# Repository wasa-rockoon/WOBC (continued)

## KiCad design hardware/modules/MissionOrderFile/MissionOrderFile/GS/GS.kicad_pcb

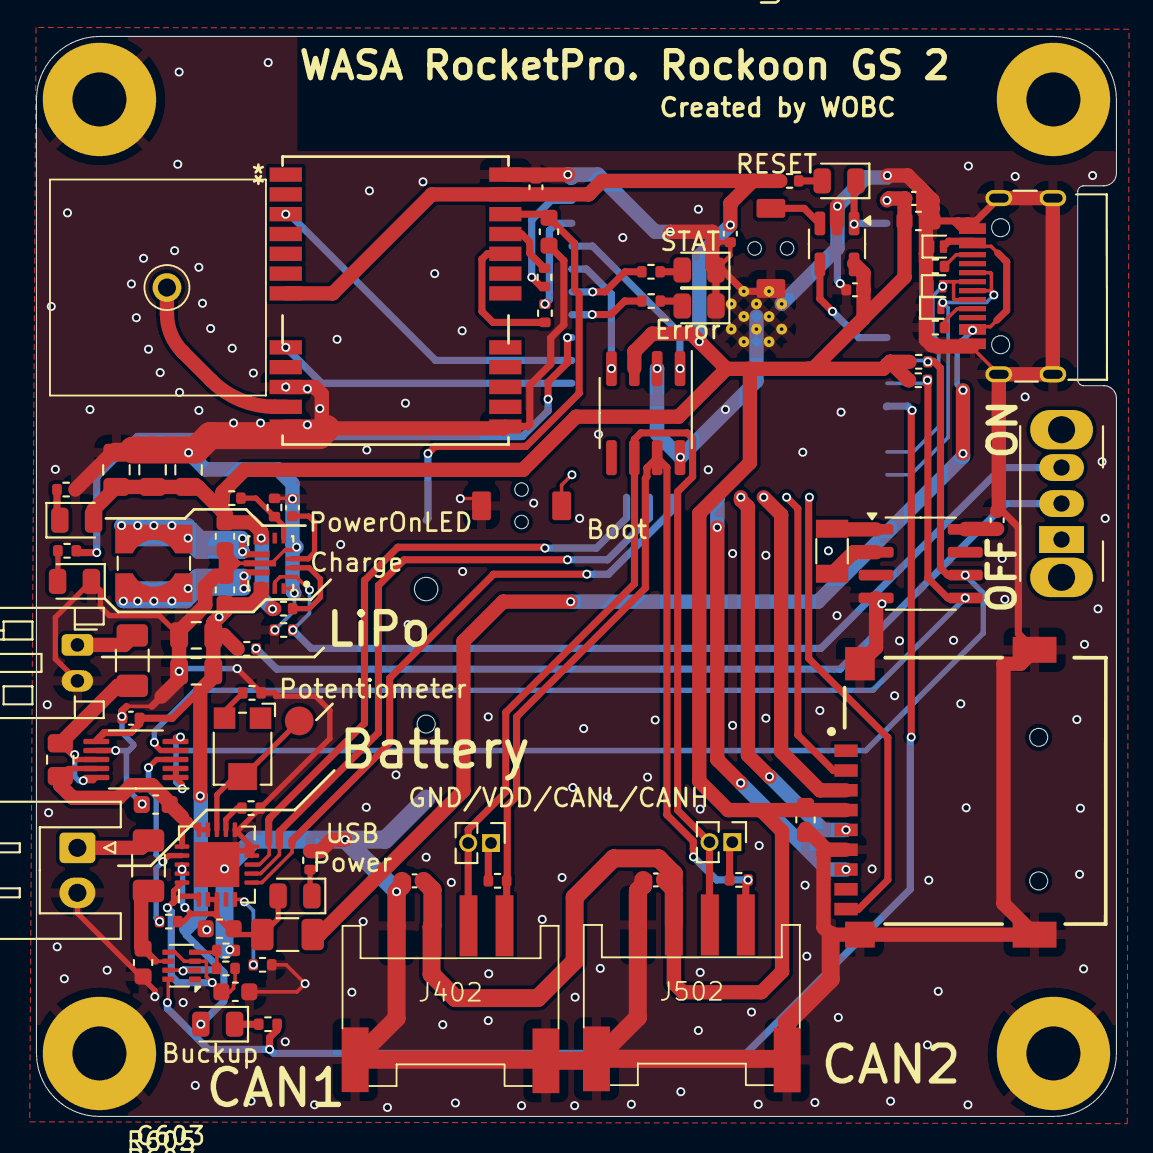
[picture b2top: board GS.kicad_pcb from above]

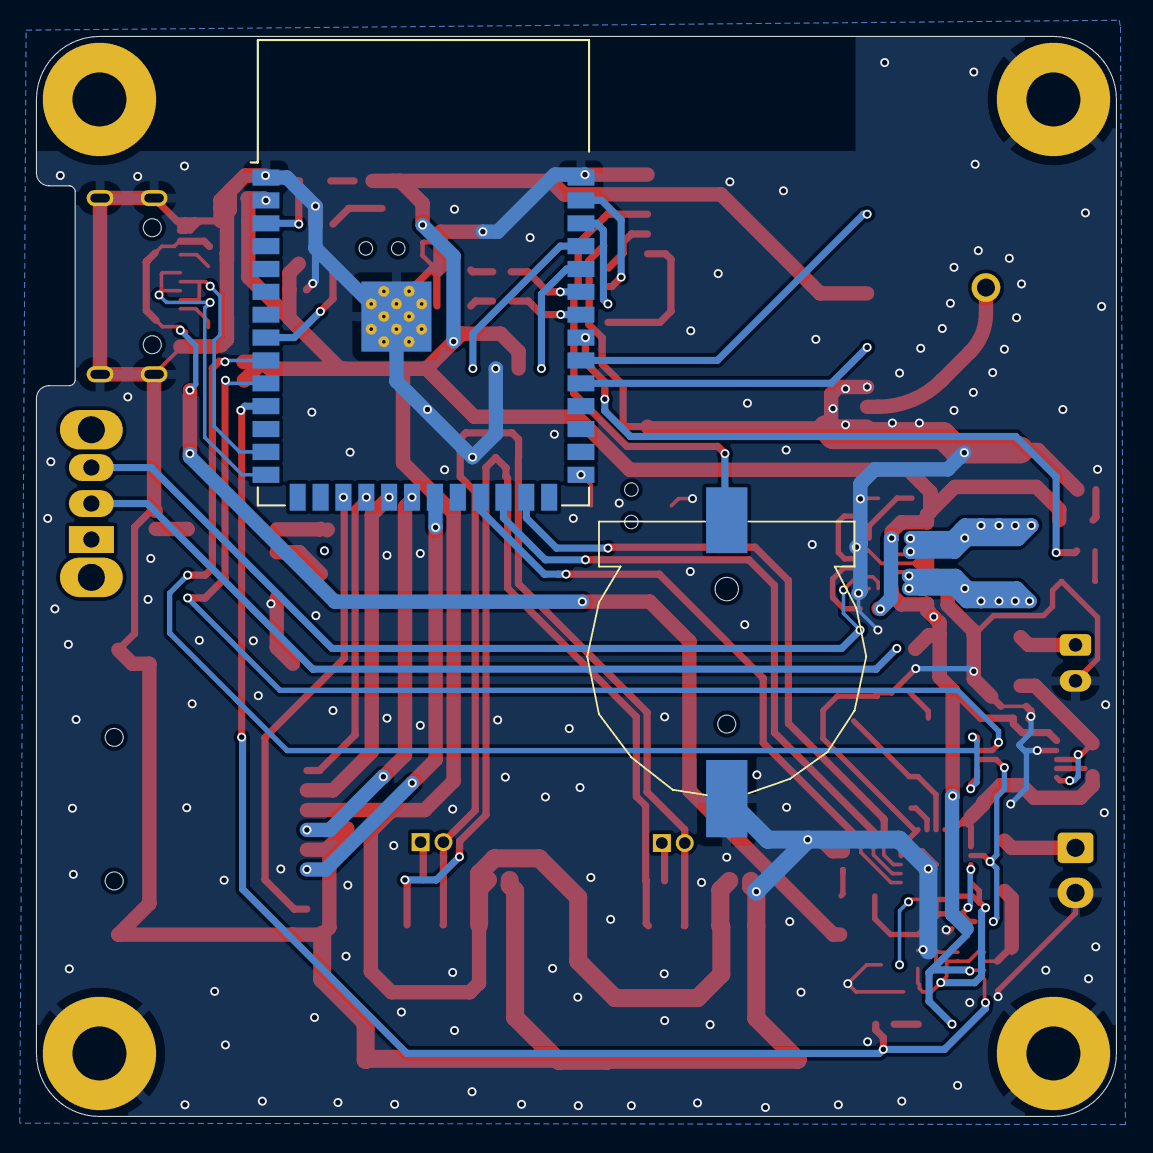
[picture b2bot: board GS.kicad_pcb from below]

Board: 2 copper layers, 60.0 x 60.0 mm, 88 parts (2 on the bottom side), 70 nets.

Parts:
AE301: Antenna; GNSS_Antenna_1212
BT101: Battery; cr1220
C101, C203, C601, C602, C603, C606, C607, C610, C701: 10uF; C_0603_1608Metric
C201, C202, C204, C301, C401, C501, C608, C609, C702: 100nF; C_0402_1005Metric
C604, C605, C611, C612, C613: 10uF; C_0805_2012Metric
D201, D202, D203: 5V; D_SOD-882
D204: RESET; LED_0805_2012Metric
D205: ERROR; LED_0805_2012Metric
D206: STAT; LED_0805_2012Metric
F601, F602, F603: Polyfuse; Fuse_1206_3216Metric
J401, J501: Jumper; PinHeader_1x02_P1.27mm_Vertical
J402, J502: Conn_01x04_MountingPin; Grove_4P_L_SMD
J601: Battery; JST_XH_S2B-XH-A_1x02_P2.50mm_Horizontal
J602: LiPo; JST_PH_S2B-PH-K_1x02_P2.00mm_Horizontal
L601: L; L_Wuerth_WE-TPC-3816
LED601: USB Power; LED_0805_2012Metric
LED602: Backup; LED_0805_2012Metric
LED603: CHARGE; LED_0805_2012Metric
LED604: VDD; LED_0805_2012Metric
MICRO_SD701: TF-01A
R201, R202: 5.1k; R_0402_1005Metric
R203, R204, R206: 470; R_0402_1005Metric
R205, R207, R604, R609: 10k; R_0402_1005Metric
R301, R302: 33; R_0402_1005Metric
R401, R501: 120; R_0402_1005Metric
R601, R602, R608, R610, R616: 1k; R_0402_1005Metric
R603, R606, R607, R611, R613: 100k; R_0402_1005Metric
R605, R615: 47k; R_0402_1005Metric
R612: 50mΩ; R_0805_2012Metric
R614: 15k; R_0402_1005Metric
RV601: 10k; Potentiometer_Bourns_TC33X_Vertical
SW201, SW202: RESET_sw; TVAF06-A020B-R
SW601: Power Switch; SW_Slide_SPDT_Angled_CK_OS102011MA1Q
U201: TPS3820; SOT-23-5
U202: SN65HVD230; SOIC-8_3.9x4.9mm_P1.27mm
U203: ESP32-S3-WROOM-1
U301: NEO-M9N-00B; ATGM332D-5N31
U601: MCP73871-1CC; QFN-20-1EP_4x4mm_P0.5mm_EP2.5x2.5mm
U602: TPS2116DRL; SOT-583-8
U603: TPS63070RNMR; VREG_TPS63070RNMR
U604: INA226; VSSOP-10_3x3mm_P0.5mm
U701: PCF8563T; SOIC-8_3.9x4.9mm_P1.27mm
USB201: USB_C_Receptacle_USB2.0; USB_C_TYPEC-301S-ACP16X7
Y701: Crystal; Crystal_SMD_3215-2Pin_3.2x1.5mm

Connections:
+BATT: C702.2, U701.8 (VDD)
/CLK: MICRO_SD701.5 (CLK), U203.20 (GPIO12/TOUCH12/ADC2_CH1/FSPICLK/FSPIIO6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)
/DET: MICRO_SD701.CD1 (CD), U203.17 (GPIO9/TOUCH9/ADC1_CH8/FSPIHD/SUBSPIHD)
/ESP32/CANH: J402.1, J502.1, R401.2, R501.2, U202.7 (CANH)
/ESP32/CANL: J401.2, J402.2, J501.2, J502.2, U202.6 (CANL)
/ESP32/CAN_RX: U202.4 (R), U203.36 (U0RXD/GPIO44/CLK_OUT2)
/ESP32/CAN_TX: U202.1 (D), U203.37 (U0TXD/GPIO43/CLK_OUT1)
/ESP32/GPIO1/ADC1_CH0: R301.1, U203.39 (GPIO1/TOUCH1/ADC1_CH0)
/ESP32/GPIO2/ADC1_CH1: R302.1, U203.38 (GPIO2/TOUCH2/ADC1_CH1)
/ESP32/GPIO18: R608.2, U203.11 (GPIO18/U1RXD/ADC2_CH7/CLK_OUT3), U602.8 (ST)
/ESP32/GPIO38: U203.31 (GPIO38/FSPIWP/SUBSPIWP), U301.8 (RESET_N)
/ESP32/GPIO39: U203.32 (MTCK/GPIO39/CLK_OUT3/SUBSPICS1), U301.3 (TIMEPULSE)
/ESP32/GPIO40: R610.2, U203.33 (MTDO/GPIO40/CLK_OUT2)
/ESP32/USB_D+: D202.2 (A2), U203.14 (GPIO20/U1CTS/ADC2_CH9/CLK_OUT1/USB_D+), USB201.A6 (D+), USB201.B6 (D+)
/ESP32/USB_D-: D203.2 (A2), U203.13 (GPIO19/U1RTS/ADC2_CH8/CLK_OUT2/USB_D-), USB201.A7 (D-), USB201.B7 (D-)
/ESP32/VUSB: D201.2 (A2), F601.1, USB201.A4 (VBUS), USB201.A9 (VBUS), USB201.B4 (VBUS), USB201.B9 (VBUS)
/ESP32/WDI: U201.4 (WDI), U203.8 (GPIO15/U0RTS/ADC2_CH4/XTAL_32K_P)
/GPS/+BATT: BT101.1 (+), C101.2, U301.22 (V_BCKP)
/MISO: MICRO_SD701.7 (DAT0), U203.21 (GPIO13/TOUCH13/ADC2_CH2/FSPIQ/FSPIIO7/S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)
/MOSI: MICRO_SD701.3 (CMD), U203.19 (GPIO11/TOUCH11/ADC2_CH0/FSPID/FSPIIO5/S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)
/PG: U203.23 (GPIO21), U601.6 (~PG)
/SCL: R205.2, U203.9 (GPIO16/U0CTS/ADC2_CH5/XTAL_32K_N), U604.1 (A1), U604.2 (A0), U604.5 (SCL), U701.6 (SCL)
/SDA: R207.2, U203.10 (GPIO17/U1TXD/ADC2_CH6), U604.4 (SDA), U701.5 (SDA)
/SS: MICRO_SD701.2 (CD/DAT3), U203.18 (GPIO10/TOUCH10/ADC1_CH9/FSPICS0/FSPIIO4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)
/STAT1: U203.25 (GPIO48/SPICLK_N/SUBSPICLK_N_DIFF), U601.8 (STAT1/~LBO)
/STAT2: U203.24 (GPIO47/SPICLK_P/SUBSPICLK_P_DIFF), U601.7 (STAT2)
GND: BT101.2 (-), C101.1, C201.1, C202.1, C203.1, C204.2, C301.1, C401.1, C501.1, C601.2, C602.2, C603.2, C604.2, C605.2, C606.2, C607.2, C608.2, C609.2, C610.2, C611.2, C612.2, C613.2, C701.2, C702.1, D201.1 (A1), D202.1 (A1), D203.1 (A1), D205.1 (K), D206.1 (K), J402.4, J402.MP (MountPin), J502.4, J502.MP (MountPin), J601.2, J602.2, LED603.1 (K), MICRO_SD701.6 (VSS), MICRO_SD701.MP1 (SHIELD), MICRO_SD701.MP2 (SHIELD), MICRO_SD701.MP3 (SHIELD), MICRO_SD701.MP4 (SHIELD), R201.2, R202.2, R601.2, R602.2, R603.2, R604.1, R605.1, R611.2, R614.1, R616.2, SW201.2, SW202.2, U201.2 (GND), U202.2 (GND), U202.8 (Rs), U203.1 (GND), U203.40 (GND), U203.41 (GND), U301.10 (GND), U301.12 (GND), U301.13 (GND), U301.24 (GND), U601.9 (~TE), U601.10 (V_{SS}), U601.11 (V_{SS}), U601.21 (V_{SS}), U602.1 (GND), U603.4 (GND), U603.10 (PGND), U603.15 (VSEL), U604.7 (GND), U701.4 (VSS), USB201.A1 (GND), USB201.A12 (GND), USB201.B1 (GND), USB201.B12 (GND), USB201.S1 (SHIELD)
GPSANT1: AE301.1 (A), U301.11 (RF_IN)
unnamed: D204.2 (A), R203.2
unnamed: D205.2 (A), R204.2
unnamed: D206.2 (A), R206.2
unnamed: J401.1, R401.1
unnamed: J501.1, R501.1
unnamed: F602.1, J601.1
unnamed: F603.2, J602.1
unnamed: C601.1, F601.2, LED601.2 (A), R606.1, U601.2 (VPCC), U601.3 (SEL), U601.18 (IN), U601.19 (IN)
unnamed: LED601.1 (K), R601.1
unnamed: C604.1, C605.1, C607.1, C608.1, LED602.2 (A), R609.1, U602.2 (VOUT), U602.7 (VOUT), U603.12_13 (VIN), U604.6 (VS)
unnamed: LED602.1 (K), R608.1
unnamed: LED603.2 (A), R610.1
unnamed: LED604.1 (K), R616.1
unnamed: R602.1, RV601.3
unnamed: R609.2, SW601.2 (B)
unnamed: R611.1, SW601.3 (C), U603.1 (PS/SYNC), U603.14 (EN)
unnamed: SW201.1, U201.3 (MR)
unnamed: SW202.1, U203.27 (GPIO0/BOOT)
unnamed: R204.1, U203.34 (MTDI/GPIO41/CLK_OUT1)
unnamed: R206.1, U203.35 (MTMS/GPIO42)
unnamed: R301.2, U301.21 (RXD_/_SPI_MOSI)
unnamed: R302.2, U301.20 (TXD_/_SPI_MISO)
unnamed: R606.2, U601.17 (CE), U604.3 (~Alert)
unnamed: RV601.2, U601.13 (PROG1)
unnamed: R603.1, U601.12 (PROG3)
unnamed: R604.2, U601.5 (THERM)
unnamed: C606.1, R612.1, U601.14 (V_{BAT}), U601.15 (V_{BAT}), U601.16 (V_{BAT_SENSE}), U604.9 (Vin-)
unnamed: C603.1, R607.1, U601.1 (OUT), U601.20 (OUT), U602.3 (VIN1), U602.5 (MODE)
unnamed: R605.2, R607.2, U602.4 (PR1)
unnamed: C602.1, F602.2, U602.6 (VIN2)
unnamed: R614.2, R615.1, U603.5 (FB)
unnamed: L601.1, U603.11 (L1)
unnamed: L601.2, U603.9 (L2)
unnamed: R613.2, U603.2 (PG)
unnamed: C609.1, U603.3 (VAUX)
unnamed: F603.1, R612.2, U604.8 (Vbus), U604.10 (Vin+)
unnamed: U701.1 (OSCI), Y701.1
unnamed: U701.2 (OSCO), Y701.2
unnamed: R201.1, USB201.A5 (CC1)
unnamed: R202.1, USB201.B5 (CC2)
RESET: D204.1 (K), U201.1 (RESET), U203.3 (EN)
VDD: C201.2, C202.2, C203.2, C204.1, C301.2, C401.2, C501.2, C610.1, C611.1, C612.1, C613.1, C701.1, J402.3, J502.3, LED604.2 (A), MICRO_SD701.4 (VDD), R203.1, R205.1, R207.1, R613.1, R615.2, U201.5 (VDD), U202.3 (VCC), U203.2 (3V3), U301.7 (V_USB), U301.23 (VCC), U603.7_8 (VOUT)

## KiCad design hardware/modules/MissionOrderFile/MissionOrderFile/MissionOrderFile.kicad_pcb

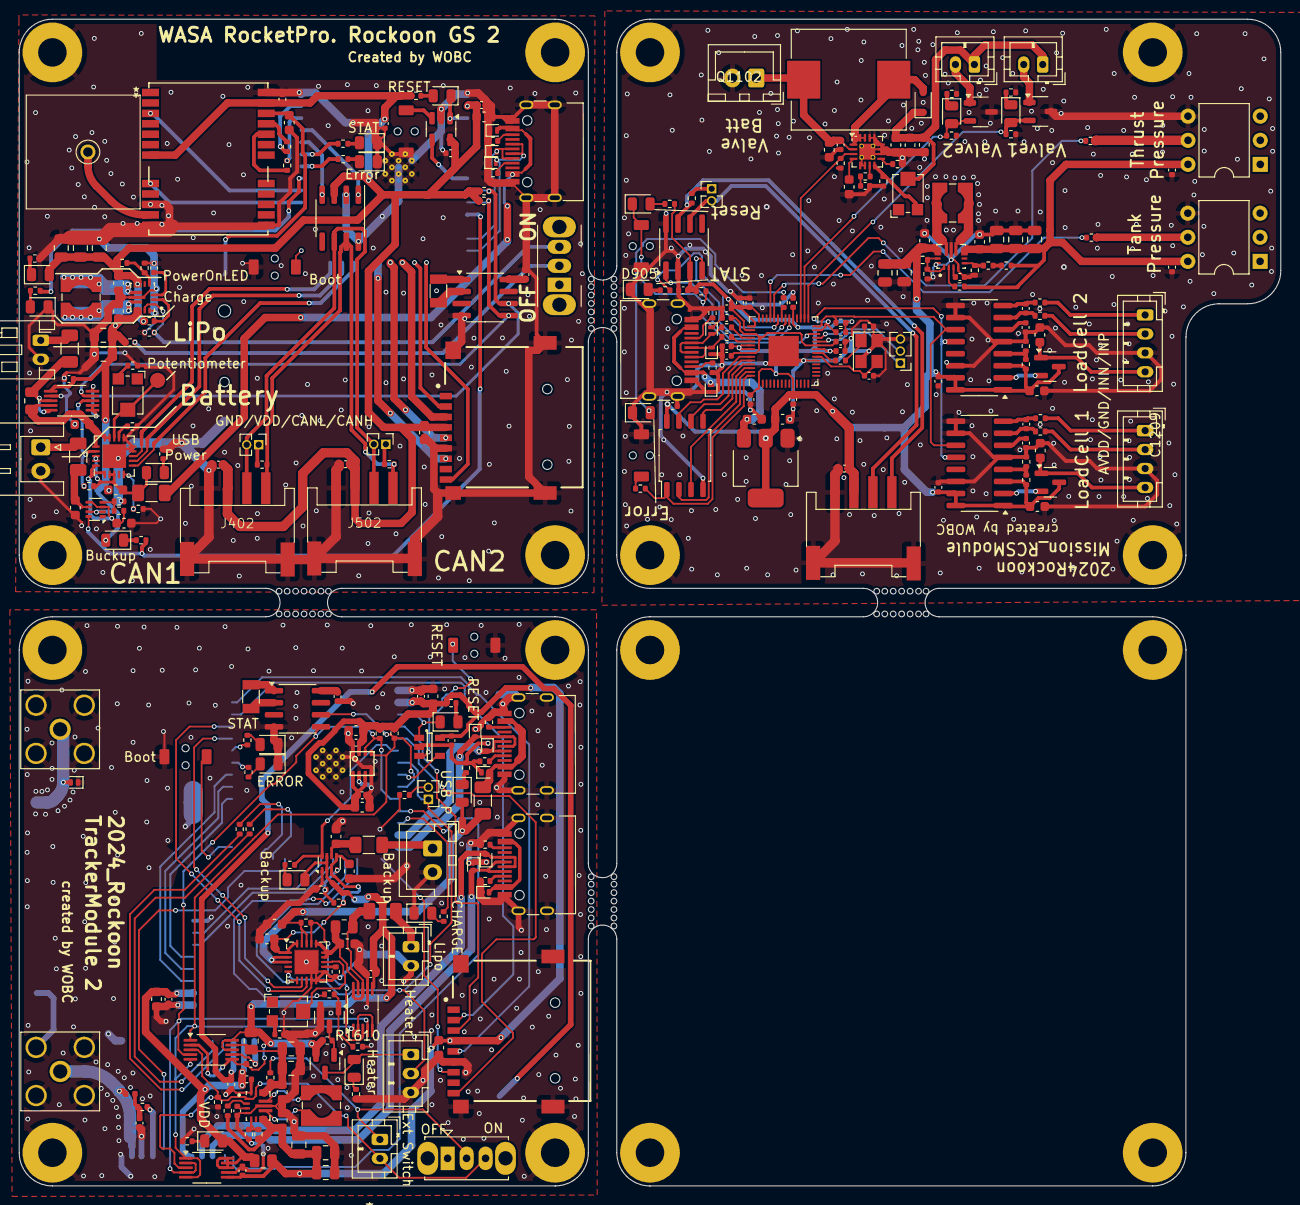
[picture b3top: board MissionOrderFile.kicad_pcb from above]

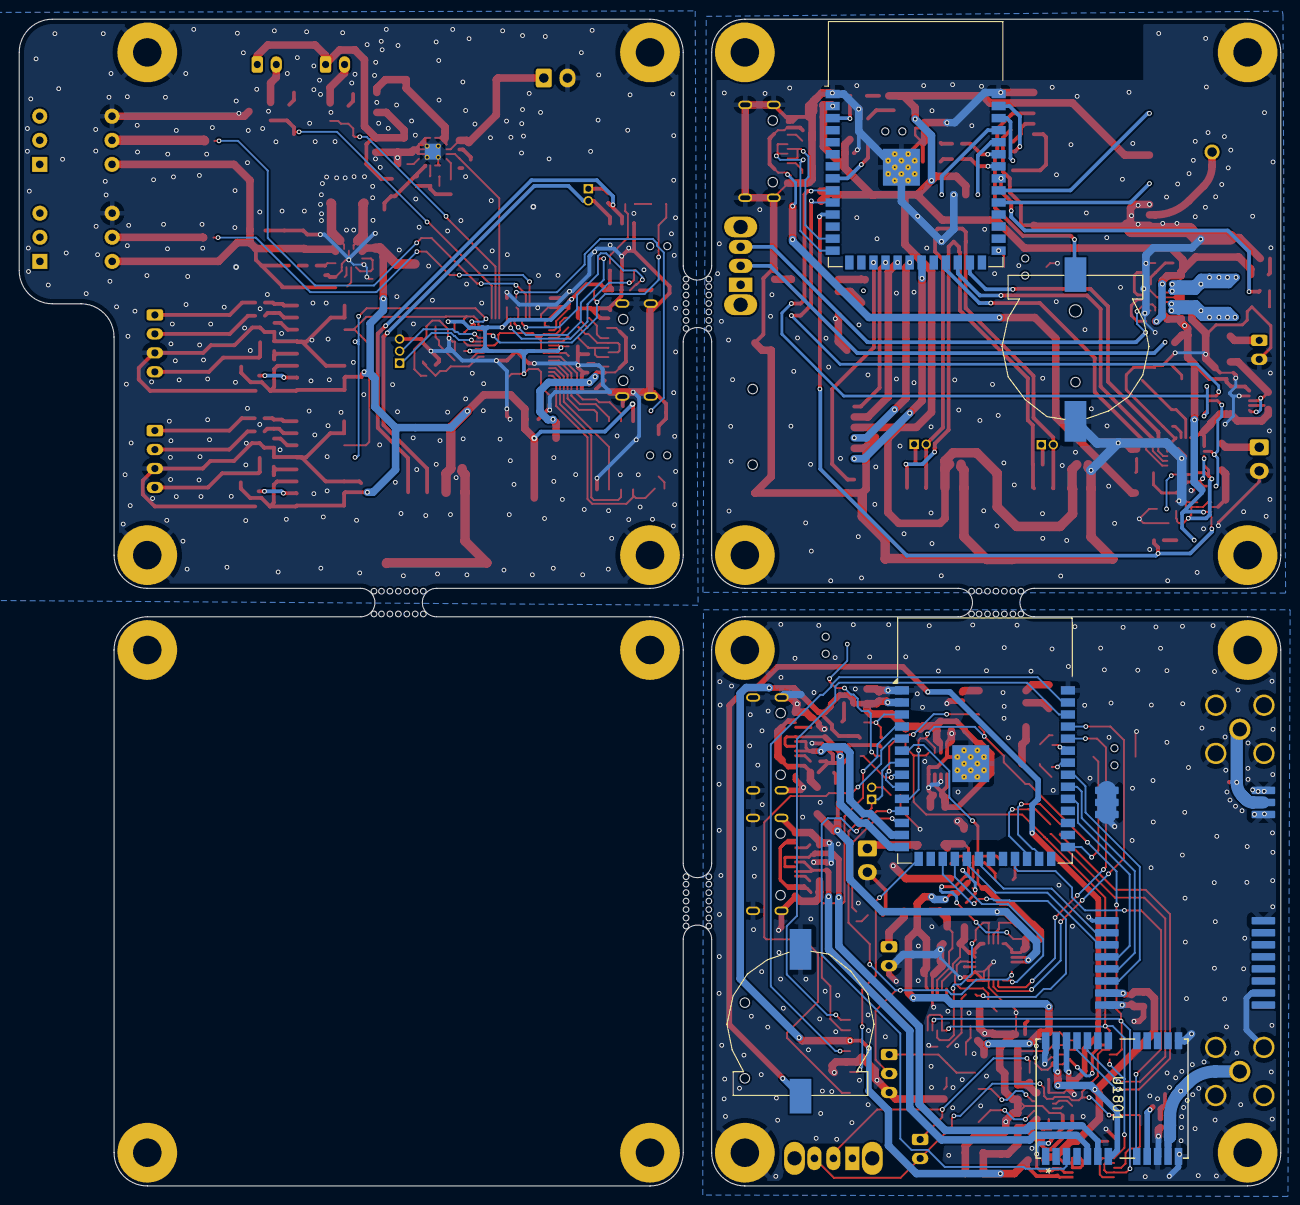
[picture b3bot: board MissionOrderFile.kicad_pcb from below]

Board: 2 copper layers, 133.0 x 123.0 mm, 322 parts (6 on the bottom side), 224 nets.

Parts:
AE301: Antenna; GNSS_Antenna_1212
BT101: Battery; cr1220
BT1501: Battery_Cell; cr1220
C101, C203, C601, C602, C603, C606, C607, C610, C701, C1102, C1203, C1205, C1301, C1304, C1401, C1404, C1601, C1602, C1603, C1605, C1606, C1610, C1612, C1901, C2102: 10uF; C_0603_1608Metric
C201, C202, C204, C301, C401, C501, C608, C609, C702, C901, C902, C905, C906, C908, C910, C911, C912, C913, C914, C915, C1001, C1204, C1209, C1210, C1604, C1609, C1611, C1616, C1702, C1703, C1801, C1802, C1803, C1902, C2101, C2103: 100nF; C_0402_1005Metric
C604, C605, C611, C612, C613: 10uF; C_0805_2012Metric
C801, C802, C2001: 10u; C_0603_1608Metric
C903, C904: 27pF; C_0402_1005Metric
C907, C909: 1uF; C_0402_1005Metric
C1101: 47nF; C_0603_1608Metric
C1103, C1104, C1302, C1303, C1305, C1402, C1403, C1405: 0.1uF; C_0402_1005Metric
C1105, C1106, C1107: 4.7uF; C_0603_1608Metric
C1201, C1202, C1206, C1207, C1208, C1607, C1608, C1613, C1614, C1615: 22uF; C_0805_2012Metric
C1701, C1704: 10μF; C_0603_1608Metric
C2002: 100n; C_0402_1005Metric
D201, D202, D203, D902, D903, D904: 5V; D_SOD-882
D204, D901, D2104: RESET; LED_0805_2012Metric
D205, D906, D2105: ERROR; LED_0805_2012Metric
D206, D905, D2106: STAT; LED_0805_2012Metric
D1101: D; D_SOD-323
D1102, D1103: LED; D_0805_2012Metric
D1801, D1802, D1803, D2101, D2102, D2103: 5V; D_SOD-882D
D2001: ESD9B5.0ST5G; D_SOD-882D
F601, F602, F603, F1601, F1602, F1603: Polyfuse; Fuse_1206_3216Metric
J401, J501, J1001: Jumper; PinHeader_1x02_P1.27mm_Vertical
J402, J502, J1002: Conn_01x04_MountingPin; Grove_4P_L_SMD
J601: Battery; JST_XH_S2B-XH-A_1x02_P2.50mm_Horizontal
J602: LiPo; JST_PH_S2B-PH-K_1x02_P2.00mm_Horizontal
J801: Conn_01x02; JST_XH_B2B-XH-A_1x02_P2.50mm_Vertical
J901: DEBUG; PinHeader_1x03_P1.27mm_Vertical
J1101, J1102: Conn_01x02; JST_PH_B2B-PH-K_1x02_P2.00mm_Vertical
J1301, J1401: Conn_01x04; JST_PH_B4B-PH-K_1x04_P2.00mm_Vertical
J1601: Battery; JST_XH_B2B-XH-A_1x02_P2.50mm_Vertical
J1602: Temp&Heater; JST_PH_B3B-PH-K_1x03_P2.00mm_Vertical
J1603: Ext Switch; JST_PH_B2B-PH-K_1x02_P2.00mm_Vertical
J1604: HeaterPin; PinHeader_1x02_P1.27mm_Vertical
J1605: LiPo; JST_PH_B2B-PH-K_1x02_P2.00mm_Vertical
J1801, J2001: SMA; SMA_Amphenol_132203-12_Horizontal
L601, L1201, L1601: L; L_Wuerth_WE-TPC-3816
L1101: L; L_Chilisin_BMRF00101040
L1801: 27nH, 300mA; L_0402_1005Metric
LED601, LED1601: USB Power; LED_0805_2012Metric
LED602, LED1603: Backup; LED_0805_2012Metric
LED603, LED1602: CHARGE; LED_0805_2012Metric
LED604, LED1605: VDD; LED_0805_2012Metric
LED1604: Heater; LED_0805_2012Metric
MICRO_SD701, MICRO_SD1901: TF-01A
Q1101, Q1102: NMOS; SOT-23-3
Q1301, Q1401: PNP; SOT-23
Q1601: Q_NPN_BEC; SOT-23
Q1602: Q_PMOS_GSD; SOT-23
R201, R202, R903, R904, R1801, R1802, R2101, R2102: 5.1k; R_0402_1005Metric
R203, R204, R206, R2103, R2104, R2106: 470; R_0402_1005Metric
R205, R207, R604, R609, R901, R909, R911, R1201, R1204, R1304, R1404, R1608, R1611, R1614, R1615, R2105, R2107: 10k; R_0402_1005Metric
R301, R302, R1804, R1805: 33; R_0402_1005Metric
R401, R501, R1001: 120; R_0402_1005Metric
R601, R602, R608, R610, R616, R902, R905, R908, R910, R912, R1104, R1105, R1107, R1205, R1207, R1208, R1601, R1602, R1603, R1609, R1612, R1622: 1k; R_0402_1005Metric
R603, R606, R607, R611, R613, R1101, R1102, R1106, R1108, R1203, R1604, R1605, R1607, R1610, R1618: 100k; R_0402_1005Metric
R605, R615, R1606, R1620: 47k; R_0402_1005Metric
R612, R1613, R1617, R1621: 50mΩ; R_0805_2012Metric
R614, R1619: 15k; R_0402_1005Metric
R906, R907: 22.4; R_0402_1005Metric
R1103: 2.2k; R_0402_1005Metric
R1202, R1616: 330k; R_0402_1005Metric
R1206: 51k; R_0402_1005Metric
R1301, R1302, R1401, R1402: 100; R_0402_1005Metric
R1303, R1403: 22k; R_0402_1005Metric
R1803: 10; R_0402_1005Metric
RV601, RV1601: 10k; Potentiometer_Bourns_TC33X_Vertical
RV1101: 20k; Potentiometer_Bourns_TC33X_Vertical
SW201, SW202, SW901: RESET_sw; TVAF06-A020B-R
SW601: Power Switch; SW_Slide_SPDT_Angled_CK_OS102011MA1Q
SW902: BOOT0; TVAF06-A020B-R
SW1601: Power Switch; SW_Slide_SPDT_Straight_CK_OS102011MS2Q
SW2101, SW2102: RESET; TVAF06-A020B-R
U201: TPS3820; SOT-23-5
U202, U901: SN65HVD230; SOIC-8_3.9x4.9mm_P1.27mm
U203, U2102: ESP32-S3-WROOM-1
U301, U1801: NEO-M9N-00B; ATGM332D-5N31
U601, U1601: MCP73871-1CC; QFN-20-1EP_4x4mm_P0.5mm_EP2.5x2.5mm
U602, U1602: TPS2116DRL; SOT-583-8
U603, U1201, U1605: TPS63070RNMR; VREG_TPS63070RNMR
U604, U1603, U1604, U1606: INA226; VSSOP-10_3x3mm_P0.5mm
U701, U1901: PCF8563T; SOIC-8_3.9x4.9mm_P1.27mm
U801: AMS1117-3.3; SOT-223-3_TabPin2
U902: W25Q128JVS; SOIC-8_5.23x5.23mm_P1.27mm
U903: RP2040; QFN-56-1EP_7x7mm_P0.4mm_EP3.2x3.2mm
U1101: WQFN-16-1EP_3x3mm_P0.5mm_EP1.68x1.68mm_ThermalVias
U1202, U1203: DIP-6_W7.62mm
U1301, U1401: HX711; SOP-16_3.9x9.9mm_P1.27mm
U1701: BME280
U2001: E220-900T22S(JP)
U2101: TPS3820; SOT_23_5
USB201, USB901, USB1801, USB2101: USB_C_Receptacle_USB2.0; USB_C_TYPEC-301S-ACP16X7
Y701, Y1901: Crystal; Crystal_SMD_3215-2Pin_3.2x1.5mm
Y901: Crystal_GND24; Crystal_SMD_3225-4Pin_3.2x2.5mm

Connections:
+BATT: C702.2, C1902.2, U701.8 (VDD), U1901.8 (VDD)
/GS/CLK: MICRO_SD701.5 (CLK), U203.20 (GPIO12/TOUCH12/ADC2_CH1/FSPICLK/FSPIIO6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)
/GS/DET: MICRO_SD701.CD1 (CD), U203.17 (GPIO9/TOUCH9/ADC1_CH8/FSPIHD/SUBSPIHD)
/GS/ESP32/CANH: J402.1, J502.1, R401.2, R501.2, U202.7 (CANH)
/GS/ESP32/CANL: J401.2, J402.2, J501.2, J502.2, U202.6 (CANL)
/GS/ESP32/CAN_RX: U202.4 (R), U203.36 (U0RXD/GPIO44/CLK_OUT2)
/GS/ESP32/CAN_TX: U202.1 (D), U203.37 (U0TXD/GPIO43/CLK_OUT1)
/GS/ESP32/GPIO1/ADC1_CH0: R301.1, U203.39 (GPIO1/TOUCH1/ADC1_CH0)
/GS/ESP32/GPIO2/ADC1_CH1: R302.1, U203.38 (GPIO2/TOUCH2/ADC1_CH1)
/GS/ESP32/GPIO18: R608.2, U203.11 (GPIO18/U1RXD/ADC2_CH7/CLK_OUT3), U602.8 (ST)
/GS/ESP32/GPIO38: U203.31 (GPIO38/FSPIWP/SUBSPIWP), U301.8 (RESET_N)
/GS/ESP32/GPIO39: U203.32 (MTCK/GPIO39/CLK_OUT3/SUBSPICS1), U301.3 (TIMEPULSE)
/GS/ESP32/GPIO40: R610.2, U203.33 (MTDO/GPIO40/CLK_OUT2)
/GS/ESP32/USB_D+: D202.2 (A2), U203.14 (GPIO20/U1CTS/ADC2_CH9/CLK_OUT1/USB_D+), USB201.A6 (D+), USB201.B6 (D+)
/GS/ESP32/USB_D-: D203.2 (A2), U203.13 (GPIO19/U1RTS/ADC2_CH8/CLK_OUT2/USB_D-), USB201.A7 (D-), USB201.B7 (D-)
/GS/ESP32/VUSB: D201.2 (A2), F601.1, USB201.A4 (VBUS), USB201.A9 (VBUS), USB201.B4 (VBUS), USB201.B9 (VBUS)
/GS/ESP32/WDI: U201.4 (WDI), U203.8 (GPIO15/U0RTS/ADC2_CH4/XTAL_32K_P)
/GS/GPS/+BATT: BT101.1 (+), C101.2, U301.22 (V_BCKP)
/GS/MISO: MICRO_SD701.7 (DAT0), U203.21 (GPIO13/TOUCH13/ADC2_CH2/FSPIQ/FSPIIO7/S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)
/GS/MOSI: MICRO_SD701.3 (CMD), U203.19 (GPIO11/TOUCH11/ADC2_CH0/FSPID/FSPIIO5/S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)
/GS/PG: U203.23 (GPIO21), U601.6 (~PG)
/GS/SCL: R205.2, U203.9 (GPIO16/U0CTS/ADC2_CH5/XTAL_32K_N), U604.1 (A1), U604.2 (A0), U604.5 (SCL), U701.6 (SCL)
/GS/SDA: R207.2, U203.10 (GPIO17/U1TXD/ADC2_CH6), U604.4 (SDA), U701.5 (SDA)
/GS/SS: MICRO_SD701.2 (CD/DAT3), U203.18 (GPIO10/TOUCH10/ADC1_CH9/FSPICS0/FSPIIO4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)
/GS/STAT1: U203.25 (GPIO48/SPICLK_N/SUBSPICLK_N_DIFF), U601.8 (STAT1/~LBO)
/GS/STAT2: U203.24 (GPIO47/SPICLK_P/SUBSPICLK_P_DIFF), U601.7 (STAT2)
/RCS/IF/CANH: J1002.1, R1001.2, U901.7 (CANH)
/RCS/IF/CANL: J1001.2, J1002.2, U901.6 (CANL)
/RCS/RCS/RCS_EN: R1101.1, U903.31 (GPIO20), U1101.3 (EN)
/RCS/RCS/valve1: D1102.2 (A), Q1101.2 (G), R1106.1, U903.30 (GPIO19)
/RCS/RCS/valve2: D1103.2 (A), Q1102.2 (G), R1108.1, U903.29 (GPIO18)
/RCS/RP2040/CAN_RX: U901.4 (R), U903.35 (GPIO23)
/RCS/RP2040/CAN_TX: U901.1 (D), U903.34 (GPIO22)
/RCS/RP2040/GPIO26_ADC0: R1207.2, U903.38 (GPIO26_ADC0)
/RCS/RP2040/GPIO27_ADC1: R1208.2, U903.39 (GPIO27_ADC1)
/RCS/RP2040/USB_D+: D903.2 (A2), R906.1, USB901.A6 (D+), USB901.B6 (D+)
/RCS/RP2040/USB_D-: D904.2 (A2), R907.1, USB901.A7 (D-), USB901.B7 (D-)
/RCS/SCL: R911.2, U903.28 (GPIO17), U1301.11 (PD_SCK), U1401.11 (PD_SCK)
/RCS/SDA: R909.2, U903.27 (GPIO16), U1301.12 (DOUT), U1401.12 (DOUT)
/Tracker/ESP32/CAN_RX: U1601.7 (STAT2), U2102.36 (U0RXD/GPIO44/CLK_OUT2)
/Tracker/ESP32/CAN_TX: U1601.8 (STAT1/~LBO), U2102.37 (U0TXD/GPIO43/CLK_OUT1)
/Tracker/ESP32/GPIO1/ADC1_CH0: MICRO_SD1901.5 (CLK), U2102.39 (GPIO1/TOUCH1/ADC1_CH0)
/Tracker/ESP32/GPIO2/ADC1_CH1: MICRO_SD1901.2 (CD/DAT3), U2102.38 (GPIO2/TOUCH2/ADC1_CH1)
/Tracker/ESP32/GPIO3/ADC1_CH2: MICRO_SD1901.7 (DAT0), U2102.15 (GPIO3/TOUCH3/ADC1_CH2)
/Tracker/ESP32/GPIO4/ADC1_CH3: MICRO_SD1901.3 (CMD), U2102.4 (GPIO4/TOUCH4/ADC1_CH3)
/Tracker/ESP32/GPIO5/ADC1_CH4: MICRO_SD1901.CD1 (CD), U2102.5 (GPIO5/TOUCH5/ADC1_CH4)
/Tracker/ESP32/GPIO6/ADC1_CH5: R1609.2, U1602.8 (ST), U2102.6 (GPIO6/TOUCH6/ADC1_CH5)
/Tracker/ESP32/GPIO7/ADC1_CH6: J1602.2, J1604.1, U1601.5 (THERM), U2102.7 (GPIO7/TOUCH7/ADC1_CH6)
/Tracker/ESP32/GPIO8/ADC1_CH7: R1602.2, U2102.12 (GPIO8/TOUCH8/ADC1_CH7/SUBSPICS1)
/Tracker/ESP32/GPIO9/ADC1_CH8: R1608.2, U2102.17 (GPIO9/TOUCH9/ADC1_CH8/FSPIHD/SUBSPIHD)
/Tracker/ESP32/GPIO10/ADC1_CH9: U1601.6 (~PG), U2102.18 (GPIO10/TOUCH10/ADC1_CH9/FSPICS0/FSPIIO4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)
/Tracker/ESP32/GPIO11: U2001.6 (M1), U2102.19 (GPIO11/TOUCH11/ADC2_CH0/FSPID/FSPIIO5/S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)
/Tracker/ESP32/GPIO12: U2001.5 (M0), U2102.20 (GPIO12/TOUCH12/ADC2_CH1/FSPICLK/FSPIIO6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)
/Tracker/ESP32/GPIO18: U1801.3 (TIMEPULSE), U2102.11 (GPIO18/U1RXD/ADC2_CH7/CLK_OUT3)
/Tracker/ESP32/GPIO21: U1801.8 (RESET_N), U2102.23 (GPIO21)
/Tracker/ESP32/GPIO38: U2001.7 (RXD), U2102.31 (GPIO38/FSPIWP/SUBSPIWP)
/Tracker/ESP32/GPIO39: U2001.8 (TXD), U2102.32 (MTCK/GPIO39/CLK_OUT3/SUBSPICS1)
/Tracker/ESP32/GPIO40: U2001.9 (AUX), U2102.33 (MTDO/GPIO40/CLK_OUT2)
/Tracker/ESP32/GPIO47: R1805.1, U2102.24 (GPIO47/SPICLK_P/SUBSPICLK_P_DIFF)
/Tracker/ESP32/GPIO48: R1804.1, U2102.25 (GPIO48/SPICLK_N/SUBSPICLK_N_DIFF)
/Tracker/ESP32/I2C_SCL: R2105.2, U1603.1 (A1), U1603.5 (SCL), U1604.1 (A1), U1604.2 (A0), U1604.5 (SCL), U1606.1 (A1), U1606.5 (SCL), U1701.4 (SCK), U1901.6 (SCL), U2102.9 (GPIO16/U0CTS/ADC2_CH5/XTAL_32K_N)
/Tracker/ESP32/I2C_SDA: R2107.2, U1603.4 (SDA), U1604.4 (SDA), U1606.2 (A0), U1606.4 (SDA), U1701.3 (SDI), U1901.5 (SDA), U2102.10 (GPIO17/U1TXD/ADC2_CH6)
/Tracker/ESP32/USB_D+: D2102.2 (A2), U2102.14 (GPIO20/U1CTS/ADC2_CH9/CLK_OUT1/USB_D+), USB2101.A6 (D+), USB2101.B6 (D+)
/Tracker/ESP32/USB_D-: D2103.2 (A2), U2102.13 (GPIO19/U1RTS/ADC2_CH8/CLK_OUT2/USB_D-), USB2101.A7 (D-), USB2101.B7 (D-)
/Tracker/ESP32/VUSB: D2101.2 (A2), F1601.1, USB2101.A4 (VBUS), USB2101.A9 (VBUS), USB2101.B4 (VBUS), USB2101.B9 (VBUS)
/Tracker/ESP32/WDI: U2101.4 (WDI), U2102.8 (GPIO15/U0RTS/ADC2_CH4/XTAL_32K_P)
/Tracker/GPSActive/+BATT: BT1501.1 (+), C1803.2, U1801.22 (V_BCKP)
/Tracker/GPSActive/USB_D+: D1802.2 (A2), U1801.6 (USB_DP), USB1801.A6 (D+), USB1801.B6 (D+)
/Tracker/GPSActive/USB_D-: D1803.2 (A2), U1801.5 (USB_DM), USB1801.A7 (D-), USB1801.B7 (D-)
/Tracker/Lipo/PROG: RV1601.2, U1601.13 (PROG1)
GND: BT101.2 (-), BT1501.2 (-), C101.1, C201.1, C202.1, C203.1, C204.2, C301.1, C401.1, C501.1, C601.2, C602.2, C603.2, C604.2, C605.2, C606.2, C607.2, C608.2, C609.2, C610.2, C611.2, C612.2, C613.2, C701.2, C702.1, C801.2, C802.2, C901.1, C902.1, C903.1, C904.1, C905.2, C906.2, C907.1, C908.2, C909.1, C910.2, C911.2, C912.2, C913.2, C914.2, C915.2, C1001.1, C1101.2, C1102.2, C1103.2, C1104.2, C1105.2, C1106.2, C1107.2, C1201.2, C1202.2, C1203.2, C1204.2, C1205.2, C1206.2, C1207.2, C1208.2, C1209.2, C1210.2, C1301.2, C1303.2, C1304.2, C1305.2, C1401.2, C1403.2, C1404.2, C1405.2, C1601.2, C1602.2, C1603.2, C1604.2, C1605.2, C1606.2, C1607.2, C1608.2, C1609.2, C1610.2, C1611.2, C1612.2, C1613.2, C1614.2, C1615.2, C1616.2, C1701.2, C1702.2, C1703.2, C1704.2, C1801.2, C1802.1, C1803.1, C1901.2, C1902.1, C2001.2, C2002.2, C2101.1, C2102.1, C2103.2, D201.1 (A1), D202.1 (A1), D203.1 (A1), D205.1 (K), D206.1 (K), D902.1 (A1), D903.1 (A1), D904.1 (A1), D905.1 (K), D906.1 (K), D1801.1 (A1), D1802.1 (A1), D1803.1 (A1), D2001.1 (A1), D2101.1 (A1), D2102.1 (A1), D2103.1 (A1), D2105.1 (K), D2106.1 (K), J402.4, J402.MP (MountPin), J502.4, J502.MP (MountPin), J601.2, J602.2, J801.2, J901.3, J1002.4, J1002.MP (MountPin), J1301.3, J1401.3, J1601.2, J1602.3, J1605.2, J1801.2 (Ext), J2001.2 (Ext), LED603.1 (K), LED1602.1 (K), MICRO_SD701.6 (VSS), MICRO_SD701.MP1 (SHIELD), MICRO_SD701.MP2 (SHIELD), MICRO_SD701.MP3 (SHIELD), MICRO_SD701.MP4 (SHIELD), MICRO_SD1901.6 (VSS), MICRO_SD1901.MP1 (SHIELD), MICRO_SD1901.MP2 (SHIELD), MICRO_SD1901.MP3 (SHIELD), MICRO_SD1901.MP4 (SHIELD), Q1101.3 (S), Q1102.3 (S), Q1601.2 (E), R201.2, R202.2, R601.2, R602.2, R603.2, R604.1, R605.1, R611.2, R614.1, R616.2, R903.2, R904.2, R1101.2, R1102.2, R1104.2, R1105.2, R1106.2, R1107.2, R1108.2, R1202.2, R1204.1, R1304.2, R1404.2, R1601.2, R1603.2, R1604.2, R1606.1, R1610.2, R1612.1, R1615.2, R1616.2, R1619.1, R1622.2, R1801.2, R1802.2, R2101.2, R2102.2, SW201.2, SW202.2, SW901.2, SW902.1, SW2101.2, SW2102.2, U201.2 (GND), U202.2 (GND), U202.8 (Rs), U203.1 (GND), U203.40 (GND), U203.41 (GND), U301.10 (GND), U301.12 (GND), U301.13 (GND), U301.24 (GND), U601.9 (~TE), U601.10 (V_{SS}), U601.11 (V_{SS}), U601.21 (V_{SS}), U602.1 (GND), U603.4 (GND), U603.10 (PGND), U603.15 (VSEL), U604.7 (GND), U701.4 (VSS), U801.1 (GND), U901.2 (GND), U901.8 (Rs), U902.4 (GND), U903.19 (TESTEN), U903.57 (GND), U1101.5 (SYNC), U1101.6 (AGND), U1101.10 (NC), U1101.11 (PGND), U1101.12 (PGND), U1101.13 (PGND), U1101.14 (NC), U1101.17 (EP), U1201.4 (GND), U1201.10 (PGND), U1201.15 (VSEL), U1202.6 (GND), U1203.6 (GND), U1301.5 (AGND), U1301.9 (INB-), U1301.10 (INB+), U1301.14 (XI), U1401.5 (AGND), U1401.9 (INB-), U1401.10 (INB+), U1401.14 (XI), U1601.9 (~TE), U1601.10 (V_{SS}), U1601.11 (V_{SS}), U1601.21 (V_{SS}), U1602.1 (GND), U1603.7 (GND), U1604.7 (GND), U1605.4 (GND), U1605.10 (PGND), U1605.15 (VSEL), U1606.7 (GND), U1701.1 (GND), U1701.5 (SDO), U1701.7 (GND), U1801.10 (GND), U1801.12 (GND), U1801.13 (GND), U1801.24 (GND), U1901.4 (VSS), U2001.1 (GND), U2001.2 (GND), U2001.3 (GND), U2001.4 (GND), U2001.11 (GND), U2001.13 (GND), U2001.19 (GND), U2001.20 (GND), U2001.22 (GND), U2101.2 (GND), U2102.1 (GND), U2102.40 (GND), U2102.41 (GND), USB201.A1 (GND), USB201.A12 (GND), USB201.B1 (GND), USB201.B12 (GND), USB201.S1 (SHIELD), USB901.A1 (GND), USB901.A12 (GND), USB901.B1 (GND), USB901.B12 (GND), USB901.S1 (SHIELD), USB1801.A1 (GND), USB1801.A12 (GND), USB1801.B1 (GND), USB1801.B12 (GND), USB1801.S1 (SHIELD), USB2101.A1 (GND), USB2101.A12 (GND), USB2101.B1 (GND), USB2101.B12 (GND), USB2101.S1 (SHIELD), Y901.2, Y901.4
GPSANT1: AE301.1 (A), J1801.1 (In), L1801.1, U301.11 (RF_IN), U1801.11 (RF_IN)
unnamed: C904.2, R908.1, Y901.1
unnamed: C1103.1, R1103.2
unnamed: C1801.1, L1801.2, R1803.2
unnamed: D204.2 (A), R203.2
unnamed: D205.2 (A), R204.2
unnamed: D206.2 (A), R206.2
unnamed: D901.2 (A), R902.2
unnamed: D905.2 (A), R910.2
unnamed: D906.2 (A), R912.2
unnamed: D1101.2 (A), L1101.2, U1101.1 (SW), U1101.15 (SW), U1101.16 (SW)
unnamed: C1105.1, C1106.1, C1107.1, D1101.1 (K), J1101.1, J1102.1, RV1101.2
unnamed: D1102.1 (K), R1104.1
unnamed: D1103.1 (K), R1107.1
unnamed: D1801.2 (A2), USB1801.A4 (VBUS), USB1801.A9 (VBUS), USB1801.B4 (VBUS), USB1801.B9 (VBUS)
unnamed: D2001.2 (A2), J2001.1 (In), U2001.21 (ANT)
unnamed: D2104.2 (A), R2103.2
unnamed: D2105.2 (A), R2104.2
unnamed: D2106.2 (A), R2106.2
unnamed: J401.1, R401.1
unnamed: J501.1, R501.1
unnamed: F602.1, J601.1
unnamed: F603.2, J602.1
unnamed: J901.1, U903.24 (SWCLK)
unnamed: J901.2, U903.25 (SWD)
unnamed: J1001.1, R1001.1
unnamed: J1101.2, Q1101.1 (D)
unnamed: J1102.2, Q1102.1 (D)
unnamed: J1301.1, R1301.1
unnamed: J1301.2, R1302.1
unnamed: C1301.1, J1301.4, Q1301.1 (C)
unnamed: J1401.1, R1401.1
unnamed: J1401.2, R1402.1
unnamed: C1401.1, J1401.4, Q1401.1 (C)
unnamed: F1602.1, J1601.1
unnamed: J1602.1, LED1604.2 (A), Q1602.3 (D)
unnamed: J1603.1, R1614.1, SW1601.2 (B)
unnamed: J1603.2, R1616.1, SW1601.3 (C), U1603.3 (~Alert), U1605.1 (PS/SYNC), U1605.14 (EN), U1606.3 (~Alert)
unnamed: J1604.2, R1615.1
unnamed: F1603.2, J1605.1
unnamed: C601.1, F601.2, LED601.2 (A), R606.1, U601.2 (VPCC), U601.3 (SEL), U601.18 (IN), U601.19 (IN)
unnamed: LED601.1 (K), R601.1
unnamed: C604.1, C605.1, C607.1, C608.1, LED602.2 (A), R609.1, U602.2 (VOUT), U602.7 (VOUT), U603.12_13 (VIN), U604.6 (VS)
unnamed: LED602.1 (K), R608.1
unnamed: LED603.2 (A), R610.1
unnamed: LED604.1 (K), R616.1
unnamed: C1601.1, F1601.2, LED1601.2 (A), R1605.1, U1601.2 (VPCC), U1601.3 (SEL), U1601.18 (IN), U1601.19 (IN)
unnamed: LED1601.1 (K), R1601.1
unnamed: LED1602.2 (A), R1602.1
unnamed: LED1603.1 (K), R1609.1
unnamed: LED1604.1 (K), R1612.2
unnamed: LED1605.1 (K), R1622.1
unnamed: Q1301.2 (B), U1301.2 (BASE)
unnamed: Q1401.2 (B), U1401.2 (BASE)
unnamed: Q1601.1 (B), R1608.1, R1610.1
unnamed: Q1601.3 (C), Q1602.1 (G), R1611.2
unnamed: R602.1, RV601.3
unnamed: R905.2, SW902.2
unnamed: R1205.2, R1206.1
unnamed: R1603.1, RV1601.3
unnamed: R609.2, SW601.2 (B)
unnamed: R611.1, SW601.3 (C), U603.1 (PS/SYNC), U603.14 (EN)
unnamed: SW201.1, U201.3 (MR)
unnamed: SW202.1, U203.27 (GPIO0/BOOT)
unnamed: R204.1, U203.34 (MTDI/GPIO41/CLK_OUT1)
unnamed: R206.1, U203.35 (MTMS/GPIO42)
unnamed: R301.2, U301.21 (RXD_/_SPI_MOSI)
unnamed: R302.2, U301.20 (TXD_/_SPI_MISO)
unnamed: R606.2, U601.17 (CE), U604.3 (~Alert)
unnamed: RV601.2, U601.13 (PROG1)
unnamed: R603.1, U601.12 (PROG3)
unnamed: R604.2, U601.5 (THERM)
unnamed: C606.1, R612.1, U601.14 (V_{BAT}), U601.15 (V_{BAT}), U601.16 (V_{BAT_SENSE}), U604.9 (Vin-)
unnamed: C603.1, R607.1, U601.1 (OUT), U601.20 (OUT), U602.3 (VIN1), U602.5 (MODE)
unnamed: R605.2, R607.2, U602.4 (PR1)
unnamed: C602.1, F602.2, U602.6 (VIN2)
unnamed: R614.2, R615.1, U603.5 (FB)
unnamed: L601.1, U603.11 (L1)
unnamed: L601.2, U603.9 (L2)
unnamed: R613.2, U603.2 (PG)
unnamed: C609.1, U603.3 (VAUX)
unnamed: F603.1, R612.2, U604.8 (Vbus), U604.10 (Vin+)
unnamed: U701.1 (OSCI), Y701.1
unnamed: U701.2 (OSCO), Y701.2
unnamed: U902.6 (CLK), U903.52 (QSPI_SCLK)
unnamed: U902.5 (DI(IO0)), U903.53 (QSPI_SD0)
unnamed: U902.2 (DO(IO1)), U903.55 (QSPI_SD1)
unnamed: U902.3 (IO2), U903.54 (QSPI_SD2)
unnamed: U902.7 (IO3), U903.51 (QSPI_SD3)
unnamed: R905.1, U902.1 (~CS), U903.56 (QSPI_SS)
unnamed: R912.1, U903.36 (GPIO24)
unnamed: R910.1, U903.37 (GPIO25)
unnamed: R907.2, U903.46 (USB_DM)
unnamed: R906.2, U903.47 (USB_DP)
unnamed: C905.1, C906.1, C907.2, U903.23 (DVDD), U903.45 (VREG_VOUT), U903.50 (DVDD)
unnamed: C903.2, U903.20 (XIN), Y901.3
unnamed: R908.2, U903.21 (XOUT)
unnamed: R1103.1, U1101.7 (COMP)
unnamed: R1105.1, RV1101.3, U1101.8 (FB)
unnamed: R1102.1, U1101.9 (FREQ)
unnamed: C1101.1, U1101.4 (SS)
unnamed: R1201.1, R1202.1, U1201.1 (PS/SYNC), U1201.14 (EN)
unnamed: R1204.2, R1205.1, U1201.5 (FB)
unnamed: L1201.1, U1201.11 (L1)
unnamed: L1201.2, U1201.9 (L2)
unnamed: R1203.2, U1201.2 (PG)
unnamed: C1204.1, U1201.3 (VAUX)
unnamed: C1205.1, C1206.1, C1207.1, C1208.1, C1209.1, C1210.1, R1203.1, R1206.2, U1201.7_8 (VOUT), U1202.4 (VDD), U1203.4 (VDD)
unnamed: R1207.1, U1202.5 (VOUT)
unnamed: R1208.1, U1203.5 (VOUT)
unnamed: C1302.1, R1301.2, U1301.8 (INA+)
unnamed: C1302.2, R1302.2, U1301.7 (INA-)
unnamed: C1303.1, U1301.6 (VBG)
unnamed: R1303.2, R1304.1, U1301.4 (VFB)
unnamed: C1402.1, R1401.2, U1401.8 (INA+)
unnamed: C1402.2, R1402.2, U1401.7 (INA-)
unnamed: C1403.1, U1401.6 (VBG)
unnamed: R1403.2, R1404.1, U1401.4 (VFB)
unnamed: R1605.2, U1601.17 (CE), U1604.3 (~Alert)
unnamed: R1604.1, U1601.12 (PROG3)
unnamed: C1606.1, R1617.1, U1601.14 (V_{BAT}), U1601.15 (V_{BAT}), U1601.16 (V_{BAT_SENSE}), U1604.9 (Vin-)
unnamed: C1603.1, C1605.1, R1607.1, U1601.1 (OUT), U1601.20 (OUT), U1602.3 (VIN1), U1602.5 (MODE)
unnamed: R1606.2, R1607.2, U1602.4 (PR1)
unnamed: C1602.1, F1602.2, U1602.6 (VIN2)
unnamed: C1607.1, C1608.1, C1610.1, R1613.2, R1614.2, U1603.9 (Vin-), U1605.12_13 (VIN)
unnamed: F1603.1, R1617.2, U1604.8 (Vbus), U1604.10 (Vin+)
unnamed: R1619.2, R1620.1, U1605.5 (FB)
unnamed: L1601.1, U1605.11 (L1)
unnamed: L1601.2, U1605.9 (L2)
unnamed: R1618.2, U1605.2 (PG)
unnamed: C1611.1, U1605.3 (VAUX)
unnamed: R1804.2, U1801.21 (RXD_/_SPI_MOSI)
unnamed: R1805.2, U1801.20 (TXD_/_SPI_MISO)
unnamed: U1901.1 (OSCI), Y1901.1
unnamed: U1901.2 (OSCO), Y1901.2
unnamed: SW2101.1, U2101.3 (MR)
unnamed: SW2102.1, U2102.27 (GPIO0/BOOT)
unnamed: R2104.1, U2102.34 (MTDI/GPIO41/CLK_OUT1)
unnamed: R2106.1, U2102.35 (MTMS/GPIO42)
unnamed: R201.1, USB201.A5 (CC1)
unnamed: R202.1, USB201.B5 (CC2)
unnamed: R903.1, USB901.A5 (CC1)
unnamed: R904.1, USB901.B5 (CC2)
unnamed: R1801.1, USB1801.A5 (CC1)
unnamed: R1802.1, USB1801.B5 (CC2)
unnamed: R2101.1, USB2101.A5 (CC1)
unnamed: R2102.1, USB2101.B5 (CC2)
RCS_VIN: C1102.1, C1104.1, J801.1, L1101.1, U1101.2 (VIN)
RESET: D204.1 (K), D901.1 (K), D2104.1 (K), R901.2, SW901.1, U201.1 (RESET), U203.3 (EN), U903.26 (RUN), U2101.1 (RESET), U2102.3 (EN)
VBUS: C801.1, D902.2 (A2), U801.3 (VI), USB901.A4 (VBUS), USB901.A9 (VBUS), USB901.B4 (VBUS), USB901.B9 (VBUS)
VCCRF: R1803.1, U1801.9 (VCC_RF)
VDD: C201.2, C202.2, C203.2, C204.1, C301.2, C401.2, C501.2, C610.1, C611.1, C612.1, C613.1, C701.1, C802.1, C901.2, C902.2, C908.1, C909.2, C910.1, C911.1, C912.1, C913.1, C914.1, C915.1, C1001.2, C1201.1, C1202.1, C1203.1, C1304.1, C1305.1, C1404.1, C1405.1, C1612.1, C1613.1, C1614.1, C1615.1, C1616.1, C1701.1, C1702.1, C1703.1, C1704.1, C1802.2, C1901.1, C2001.1, C2002.1, C2101.2, C2102.2, C2103.1, J402.3, J502.3, J1002.3, LED604.2 (A), LED1605.2 (A), MICRO_SD701.4 (VDD), MICRO_SD1901.4 (VDD), Q1301.3 (E), Q1401.3 (E), R203.1, R205.1, R207.1, R613.1, R615.2, R901.1, R902.1, R909.1, R911.1, R1201.2, R1303.1, R1403.1, R1618.1, R1620.2, R1621.1, R1621.2, R2103.1, R2105.1, R2107.1, U201.5 (VDD), U202.3 (VCC), U203.2 (3V3), U301.7 (V_USB), U301.23 (VCC), U603.7_8 (VOUT), U801.2 (VO), U901.3 (VCC), U902.8 (VCC), U903.1 (IOVDD), U903.10 (IOVDD), U903.22 (IOVDD), U903.33 (IOVDD), U903.42 (IOVDD), U903.43 (ADC_AVDD), U903.44 (VREG_IN), U903.48 (USB_VDD), U903.49 (IOVDD), U1201.12_13 (VIN), U1301.1 (VSUP), U1301.3 (AVDD), U1301.15 (RATE), U1301.16 (DVDD), U1401.1 (VSUP), U1401.3 (AVDD), U1401.15 (RATE), U1401.16 (DVDD), U1605.7_8 (VOUT), U1606.6 (VS), U1606.8 (Vbus), U1606.9 (Vin-), U1606.10 (Vin+), U1701.2 (CSB), U1701.6 (VDDIO), U1701.8 (VDD), U1801.7 (V_USB), U1801.23 (VCC), U2001.10 (VDD), U2101.5 (VDD), U2102.2 (3V3)
VPP: C1604.1, C1609.1, LED1603.2 (A), Q1602.2 (S), R1611.1, R1613.1, U1602.2 (VOUT), U1602.7 (VOUT), U1603.2 (A0), U1603.6 (VS), U1603.8 (Vbus), U1603.10 (Vin+), U1604.6 (VS)
